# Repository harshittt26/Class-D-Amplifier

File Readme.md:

# Class D Amplifier Project

A medium-power Class D amplifier designed using AutoCAD Eagle and simulated in LTspice.  
This project demonstrates how a low-voltage audio signal is modulated, converted into a PWM signal, amplified with high efficiency, and then filtered back into a high-power audio output.

---

## Project Overview
- **Design Software**: AutoCAD Eagle (circuit & PCB design)  
- **Simulation Software**: LTspice (circuit simulation & waveform analysis)  
- **Amplifier Type**: Class D (Switching Amplifier)  
- **Output Power**: Medium power (suitable for driving standard speaker loads)  

The design follows the typical signal flow of a Class D amplifier:
1. **Triangular Carrier Generation**  
2. **Audio Input (Sine Wave Modulation)**  
3. **PWM Generation via Comparator**  
4. **Output Switching Stage**  
5. **LC Filter for Audio Recovery**

---

## Typical Signal Parameters (Theoretical Working)

### 1. Triangular Wave (Carrier)  
The triangular wave acts as a high-frequency reference signal. It is compared with the input audio to generate a pulse-width modulated (PWM) signal. Its role is to ensure that the amplifier can translate the analog audio into varying pulse widths for efficient digital switching.

### 2. Audio Input (Sine Wave)  
The audio input provides the modulating signal that carries the sound information. When compared against the triangular carrier, the instantaneous amplitude of this sine wave determines the duty cycle of the PWM pulses.

### 3. PWM Signal (Comparator Output)  
The comparator produces a digital PWM waveform by comparing the triangular carrier with the audio input. The duty cycle of the output pulses varies in direct proportion to the input audio amplitude, effectively encoding the audio signal into time-domain variations.

### 4. Output Before Filtering  
At this stage, the amplifier output consists of a high-power PWM waveform. The signal still contains the high-frequency switching component but carries the audio information embedded within the pulse widths.

### 5. Filtered Audio Output  
An LC low-pass filter removes the high-frequency carrier, leaving only the amplified audio band. This produces a clean, high-power version of the original input audio signal, which is then fed to the loudspeaker.

---

## Building & Simulation

### AutoCAD Eagle
- Design schematic and PCB layout.  
- Define component footprints for power MOSFETs, drivers, and filter stage.  

### LTspice
- Simulate triangular wave generator, comparator stage, MOSFET drivers, and LC filter.  
- Observe signal waveforms at each stage:  
  - Triangle vs. audio at comparator  
  - PWM switching output  
  - Filtered audio waveform at load  

---

## License
This project is released under the **MIT License**.  
Free for academic and personal use.  

---

## Circuit Diagram

Below is the circuit block diagram of the designed Class D Amplifier:

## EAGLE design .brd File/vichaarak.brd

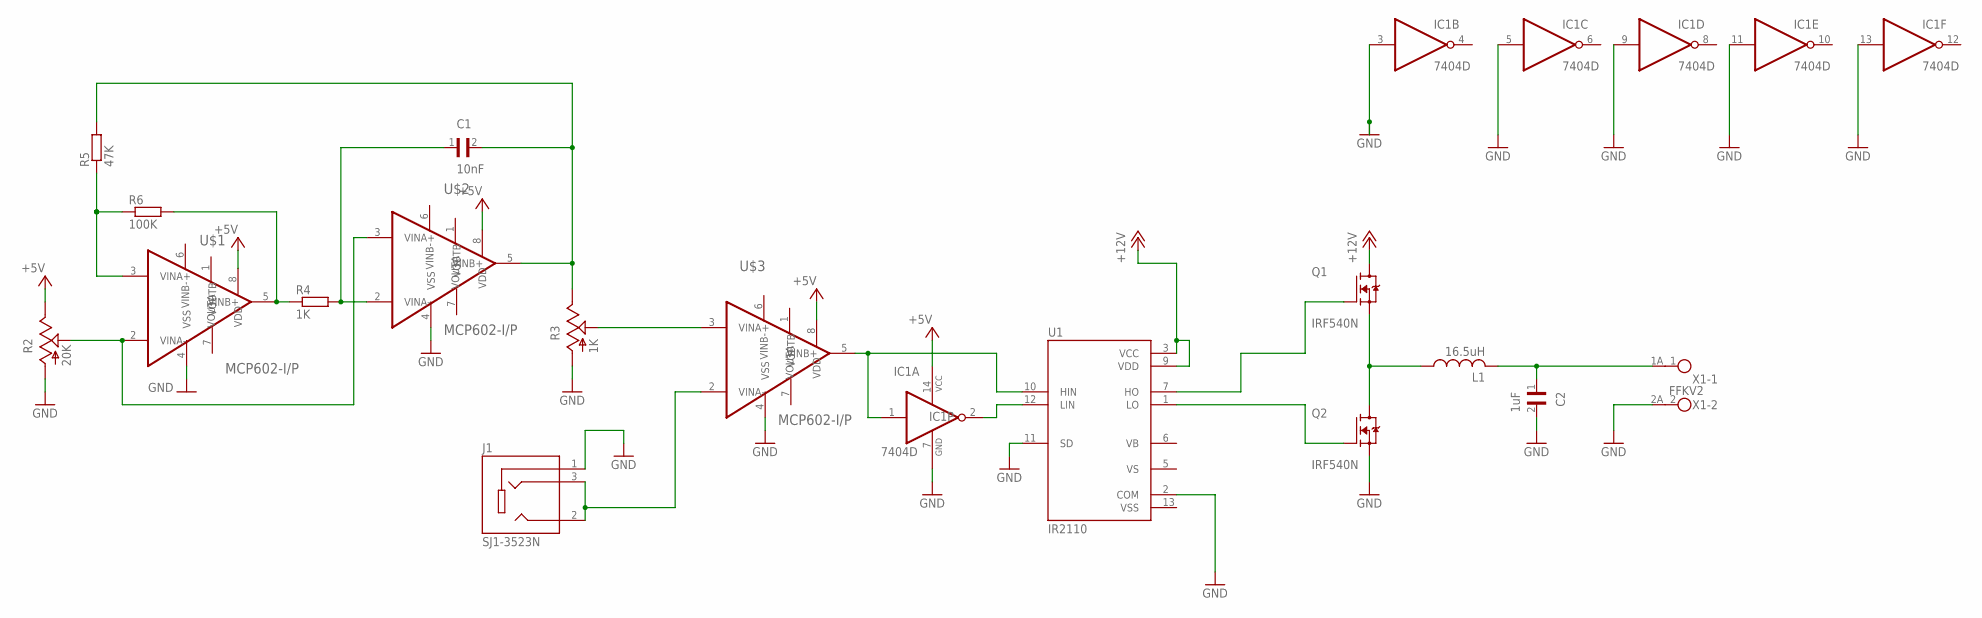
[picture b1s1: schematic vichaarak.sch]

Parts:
C1: 10nF; C0603
C2: 1uF; C0603
IC1: 7404D; SO14
J1: SJ1-3523N; CUI_SJ1-3523N
L1: 16.5uH; 0204/7
Q1, Q2: IRF540N; TO254P1054X469X1930-3
R2: 20K; PT-10
R3: 1K; PT-10
R4: 1K; R0603
R5: 47K; R0603
R6: 100K; R0603
U1: IR2110; DIP762W45P254L2019H533Q14
U$1, U$2, U$3: MCP602-I/P; DIP787W46P254L927H533Q8
X1: FFKV2

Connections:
+5V: IC1.14 (VCC), R2.E, U$1.8 (VDD), U$2.8 (VDD), U$3.8 (VDD)
+12V: Q1.2 (D), U1.3 (VCC), U1.9 (VDD)
GND: C2.2, IC1.3 (I), IC1.5 (I), IC1.7 (GND), IC1.9 (I), IC1.11 (I), IC1.13 (I), J1.1, Q2.3 (S), R2.A, R3.A, U1.2 (COM), U1.11 (SD), U$1.4 (VSS), U$2.4 (VSS), U$3.4 (VSS), X1.2A (2)
unnamed: R2.S, U$1.2 (VINA-), U$2.3 (VINA+)
unnamed: R5.1, R6.1, U$1.3 (VINA+)
unnamed: C1.2, R3.E, R5.2, U$2.5 (VINB+)
unnamed: R4.1, R6.2, U$1.5 (VINB+)
unnamed: C1.1, R4.2, U$2.2 (VINA-)
unnamed: R3.S, U$3.3 (VINA+)
unnamed: J1.2, J1.3, U$3.2 (VINA-)
unnamed: IC1.2 (O), U1.12 (LIN)
unnamed: IC1.1 (I), U1.10 (HIN), U$3.5 (VINB+)
unnamed: L1.1, Q1.3 (S), Q2.2 (D)
unnamed: Q1.1 (G), U1.7 (HO)
unnamed: Q2.1 (G), U1.1 (LO)
unnamed: C2.1, L1.2, X1.1A (2)
VSS: U1.13 (VSS)

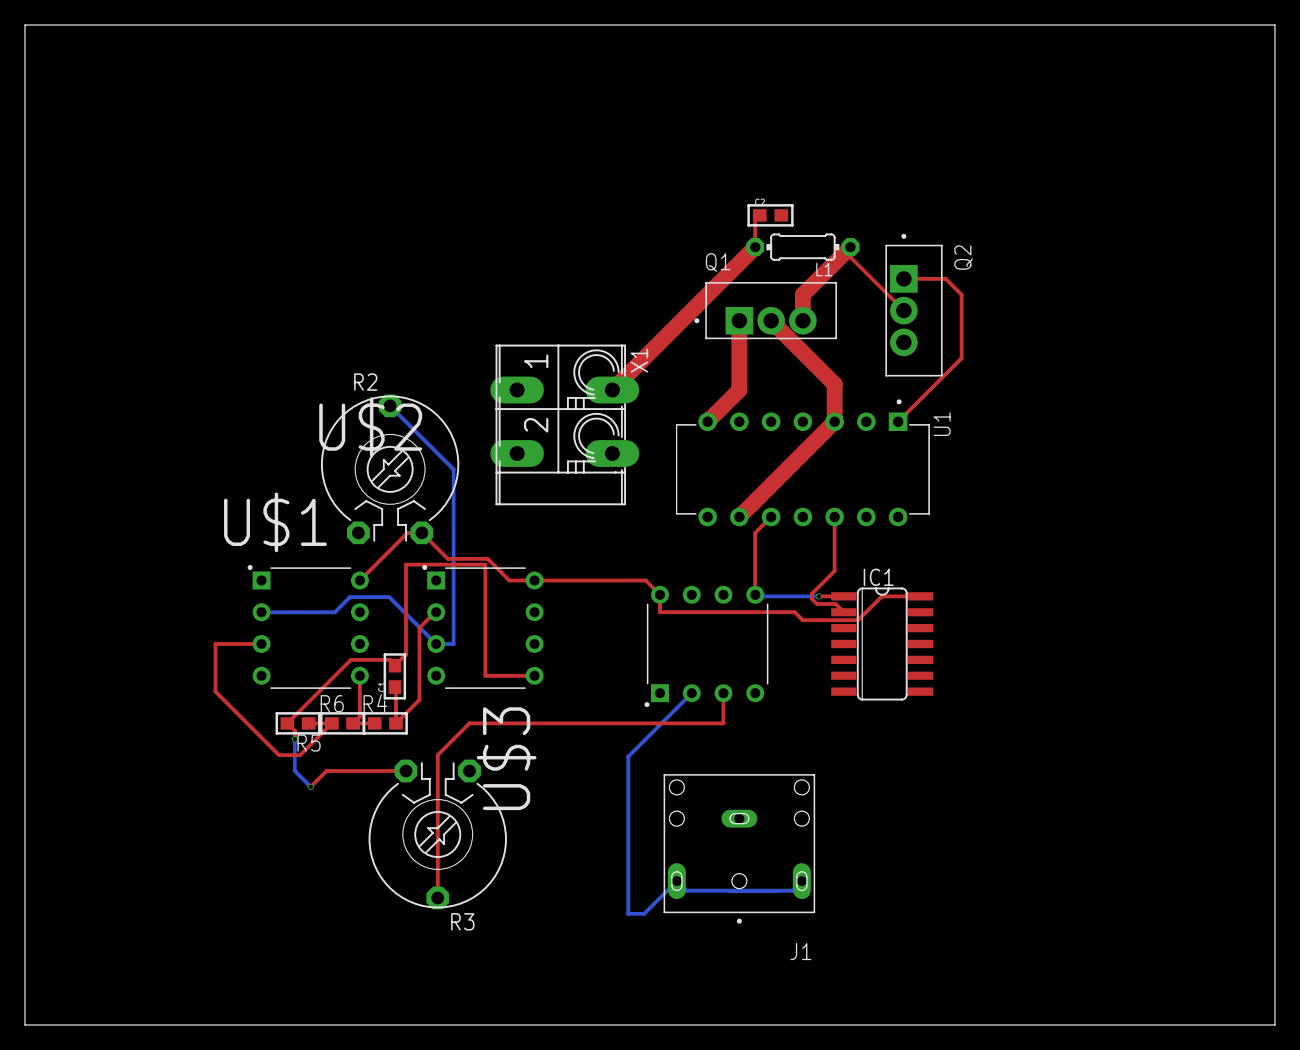
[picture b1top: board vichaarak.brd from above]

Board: 2 copper layers, 100.0 x 80.0 mm, 17 parts (0 on the bottom side), 16 nets.

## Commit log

2025-10-02 Main
    ALL THE REQUIRED FILES.
